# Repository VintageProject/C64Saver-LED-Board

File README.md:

# C64Saver-LED-Board
Draft for an indicator board that connects to bwack's C64Saver 2.4 (https://github.com/bwack/C64-Saver-bwack/tree/master/C64%20Saver%202)

Components have been tested in a prototype, PCB design is a draft, though.
Feel free to fork and design your own.

Of course, I'm not responsible for any damages your experiments may cause to your C64Saver, your C64, or any other equipment involved.

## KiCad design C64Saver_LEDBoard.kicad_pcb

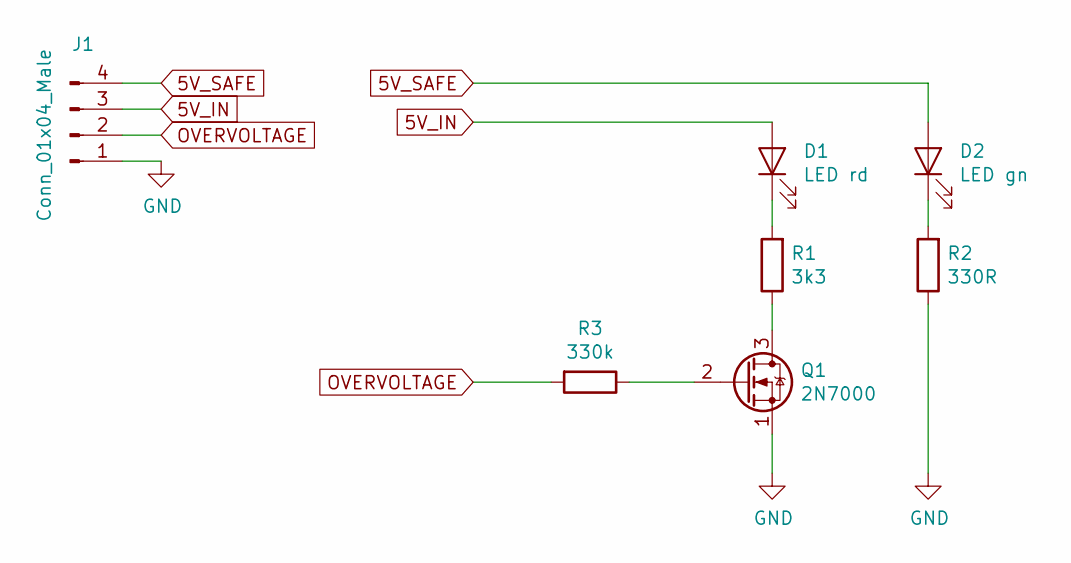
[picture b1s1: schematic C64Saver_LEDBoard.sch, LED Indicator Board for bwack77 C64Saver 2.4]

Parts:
D1: LED rd; LED_D5.0mm
D2: LED gn; LED_D5.0mm
J1: Conn_01x04_Male; PinHeader_1x04_P2.54mm_Vertical
Q1: 2N7000; TO-92_Inline
R1: 3k3; R_Axial_DIN0309_L9.0mm_D3.2mm_P2.54mm_Vertical
R2: 330R; R_Axial_DIN0309_L9.0mm_D3.2mm_P2.54mm_Vertical
R3: 330k; R_Axial_DIN0309_L9.0mm_D3.2mm_P2.54mm_Vertical

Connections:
5V_IN: D1.2 (A), J1.3
5V_SAFE: D2.2 (A), J1.4
GND: J1.1, Q1.1 (S), R2.1
unnamed: D1.1 (K), R1.2
unnamed: D2.1 (K), R2.2
unnamed: Q1.2 (G), R3.1
unnamed: Q1.3 (D), R1.1
OVERVOLTAGE: J1.2, R3.2

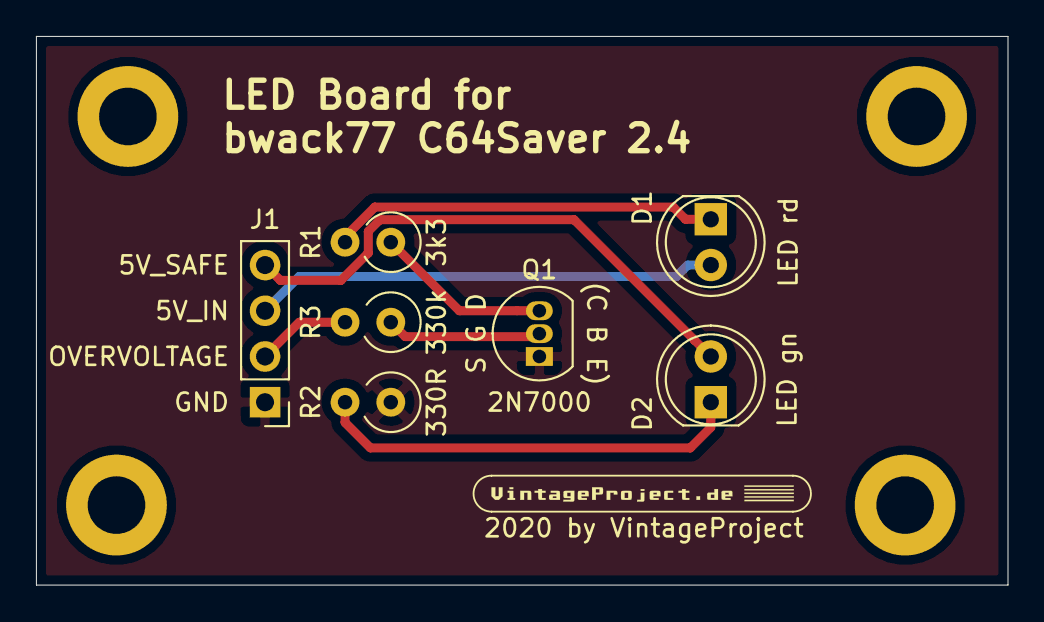
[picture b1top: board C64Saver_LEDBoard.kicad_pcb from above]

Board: 2 copper layers, 54.0 x 30.5 mm, 7 parts (0 on the bottom side), 8 nets.

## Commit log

2020-04-11 Initial commit - WIP
